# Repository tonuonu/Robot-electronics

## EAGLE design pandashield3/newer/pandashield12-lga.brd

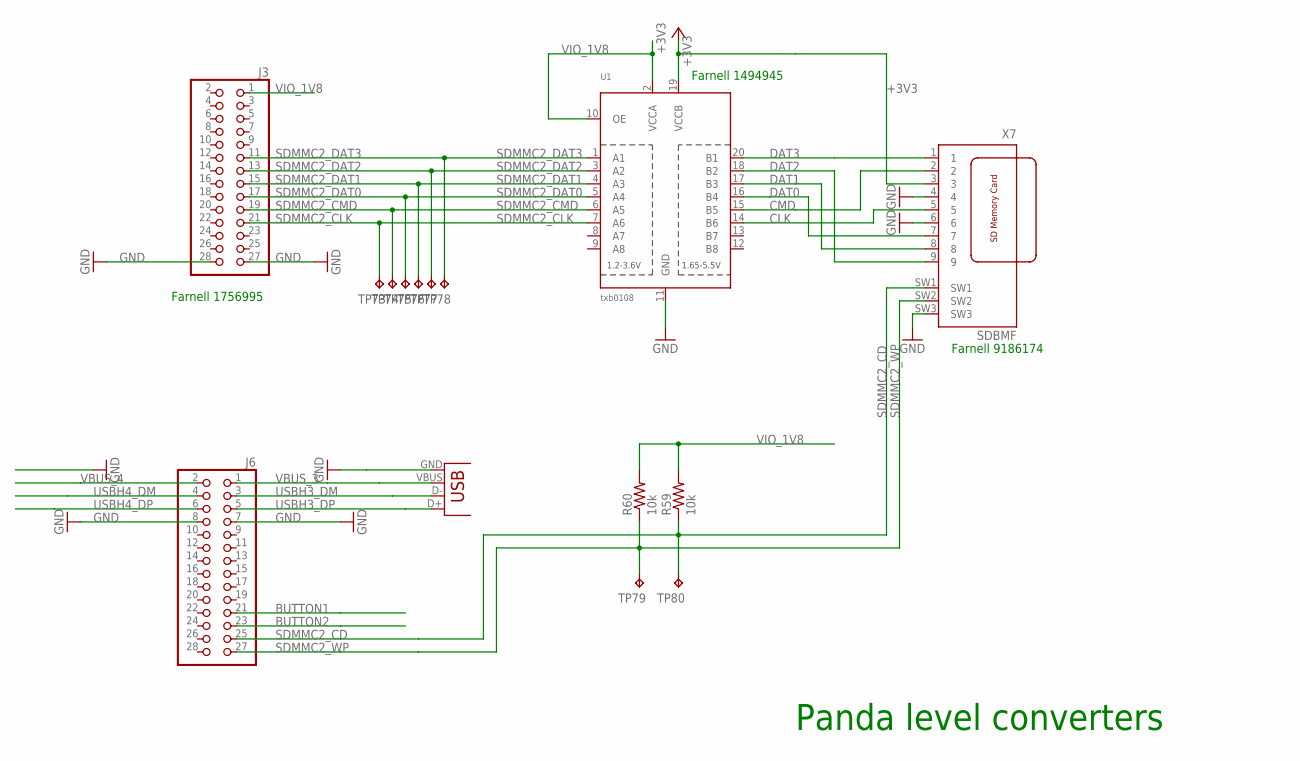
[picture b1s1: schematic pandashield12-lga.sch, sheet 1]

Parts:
J3, J6: PINHD-2X14; 2X14
R59, R60: 10k; R0603
TP73, TP74, TP75, TP76, TP77, TP78, TP79, TP80: TPB1,27; B1,27
U1: txb0108; TSSOP20
X4: USB-A-S
X7: SDBMF; SDBMF-009XXBXX2

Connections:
+3V3: U1.19 (VCCB), X7.3; also elsewhere on the board
BUTTON1: J6.21
BUTTON2: J6.23
CLK: U1.14 (B6), X7.5
CMD: U1.15 (B5), X7.2
DAT0: U1.16 (B4), X7.7
DAT1: U1.17 (B3), X7.8
DAT2: U1.18 (B2), X7.9
DAT3: U1.20 (B1), X7.1
GND: J3.27, J3.28, J6.7, J6.8, U1.11 (GND), X4.GND, X7.4, X7.6, X7.SW3; also elsewhere on the board
SDMMC2_CD: J6.25, R59.1, TP80.TP, X7.SW1
SDMMC2_CLK: J3.21, TP73.TP, U1.7 (A6)
SDMMC2_CMD: J3.19, TP74.TP, U1.6 (A5)
SDMMC2_DAT0: J3.17, TP75.TP, U1.5 (A4)
SDMMC2_DAT1: J3.15, TP76.TP, U1.4 (A3)
SDMMC2_DAT2: J3.13, TP77.TP, U1.3 (A2)
SDMMC2_DAT3: J3.11, TP78.TP, U1.1 (A1)
SDMMC2_WP: J6.27, R60.1, TP79.TP, X7.SW2
USBH3_DM: J6.3, X4.D-
USBH3_DP: J6.5, X4.D+
USBH4_DM: J6.4
USBH4_DP: J6.6
VBUS_3: J6.1, X4.VBUS
VBUS_4: J6.2
VIO_1V8: J3.1, R59.2, R60.2, U1.2 (VCCA), U1.10 (OE)

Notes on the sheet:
Panda level converters
Farnell 1494945
Farnell 9186174
Farnell 1756995

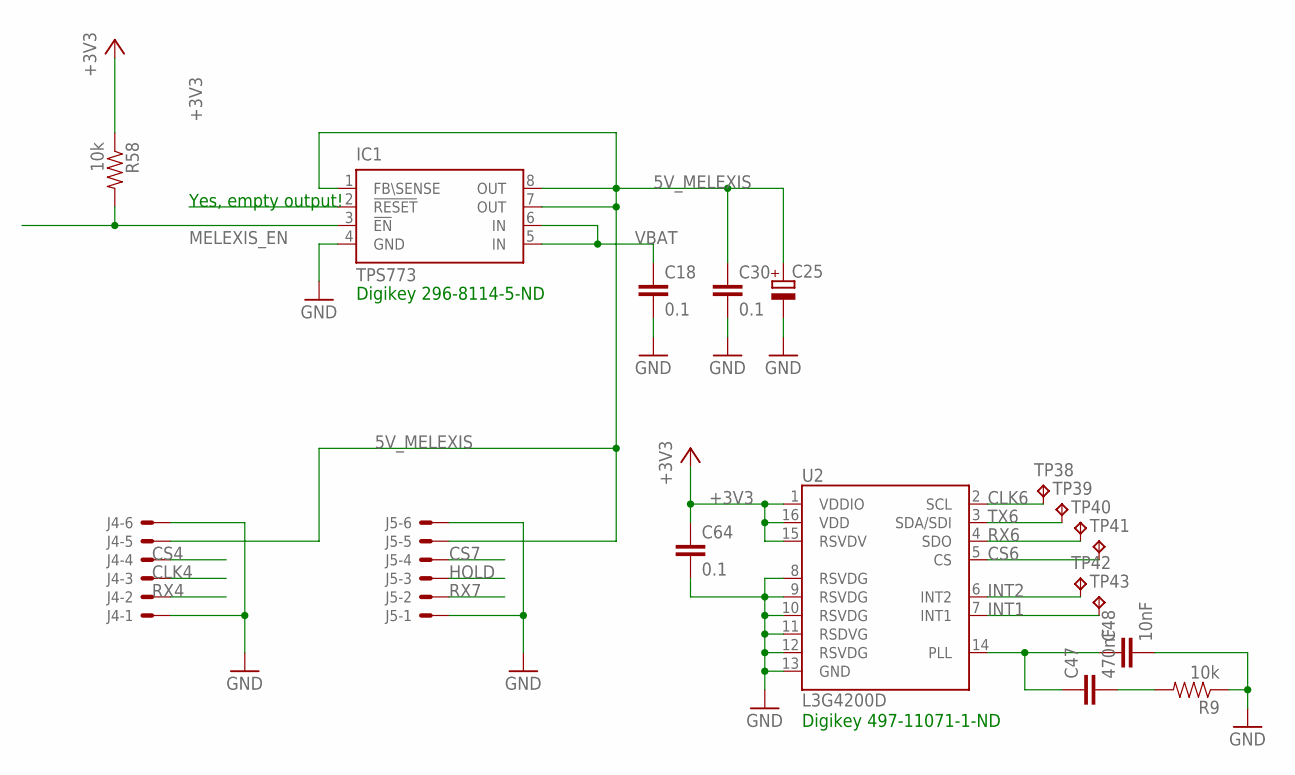
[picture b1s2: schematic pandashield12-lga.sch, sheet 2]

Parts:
C18, C30: 0.1; C0603
C25: CPOL-EUD/7343-31R; D/7343-31R
C47: 470nF; 0603-CAP
C48: 10nF; 0603-CAP
C64: 0.1; 0603-CAP
IC1: TPS773; MSOP8
J4, J5: XF2L-0625-1
R9, R58: 10k; 0603-RES
TP38, TP39, TP40, TP41, TP42, TP43: TPB1,27; B1,27
U2: L3G4200D; LGA16-4X4

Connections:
5V_MELEXIS: C25.+, C30.1, IC1.1 (FB\SENSE), IC1.7 (OUT), IC1.8 (OUT), J4.5, J5.5
+3V3: C64.1, R58.1, U2.1 (VDDIO), U2.15 (RSVDV), U2.16 (VDD); also elsewhere on the board
CLK4: J4.3; also elsewhere on the board
CLK6: TP38.TP, U2.2 (SCL); also elsewhere on the board
CS4: J4.4; also elsewhere on the board
CS6: TP41.TP, U2.5 (CS); also elsewhere on the board
CS7: J5.4; also elsewhere on the board
GND: C18.2, C25.-, C30.2, C48.2, C64.2, IC1.4 (GND), J4.1, J4.6, J5.1, J5.6, R9.1, U2.8 (RSVDG), U2.9 (RSVDG), U2.10 (RSVDG), U2.11 (RSDVG), U2.12 (RSVDG), U2.13 (GND); also elsewhere on the board
HOLD: J5.3; also elsewhere on the board
INT1: TP43.TP, U2.7 (INT1); also elsewhere on the board
INT2: TP42.TP, U2.6 (INT2); also elsewhere on the board
MELEXIS_EN: IC1.3 (!EN), R58.2; also elsewhere on the board
unnamed: C47.1, C48.1, U2.14 (PLL)
unnamed: C47.2, R9.2
RX4: J4.2; also elsewhere on the board
RX6: TP40.TP, U2.4 (SDO); also elsewhere on the board
RX7: J5.2; also elsewhere on the board
TX6: TP39.TP, U2.3 (SDA/SDI); also elsewhere on the board
VBAT: C18.1, IC1.5 (IN), IC1.6 (IN); also elsewhere on the board

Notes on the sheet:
Digikey 296-8114-5-ND
Digikey 497-11071-1-ND
Yes, empty output!

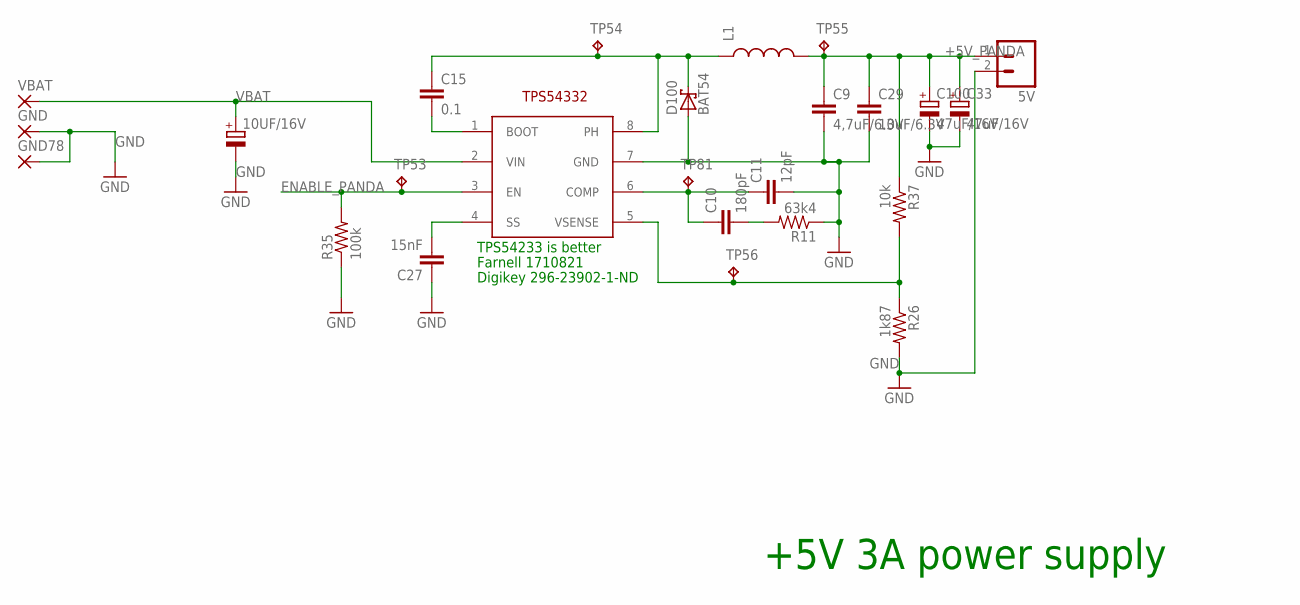
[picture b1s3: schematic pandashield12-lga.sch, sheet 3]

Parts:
5V: M02; 02P
10UF/16V: CPOL-EUC/6032-28R; C/6032-28R
C9: 4,7uF/6.3V; C0805
C10: 180pF; C0603
C11: 12pF; C0603
C15: 0.1; C0603
C27: 15nF; C0603
C29: 10uF/6.3V; 1210
C33, C100: 47uF/16V; C/6032-28R
D100: BAT54; SOT23
GND, GND78: 3,81/1,4
L1: INDUCTORCR75; CR75
R11: 63k4; R0603
R26: 1k87; R0603
R35: 100k; R0603
R37: 10k; R0603
TP53, TP54, TP55, TP56, TP81: TPB1,27; B1,27
U$3: TPS54233; SO8
VBAT: 3,81/1,4

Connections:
+5V_PANDA: 5V.1, C9.1, C29.1, C33.+, C100.+, L1.P$2 (2), R37.1, TP55.TP
ENABLE_PANDA: R35.2, TP53.TP, U$3.3 (EN); also elsewhere on the board
GND: 5V.2, 10UF/16V.-, C9.2, C11.2, C27.1, C29.2, C33.-, C100.-, D100.1 (A), GND.1, GND78.1, R11.1, R26.2, R35.1, U$3.7 (GND); also elsewhere on the board
unnamed: C10.1, C11.1, TP81.TP, U$3.6 (COMP)
unnamed: C10.2, R11.2
unnamed: C27.2, U$3.4 (SS)
unnamed: C15.2, U$3.1 (BOOT)
unnamed: R26.1, R37.2, TP56.TP, U$3.5 (VSENSE)
unnamed: C15.1, D100.3 (C), L1.P$1 (1), TP54.TP, U$3.8 (PH)
VBAT: 10UF/16V.+, U$3.2 (VIN), VBAT.1; also elsewhere on the board

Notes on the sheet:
+5V 3A power supply
TPS54233 is better
Farnell 1710821
Digikey 296-23902-1-ND

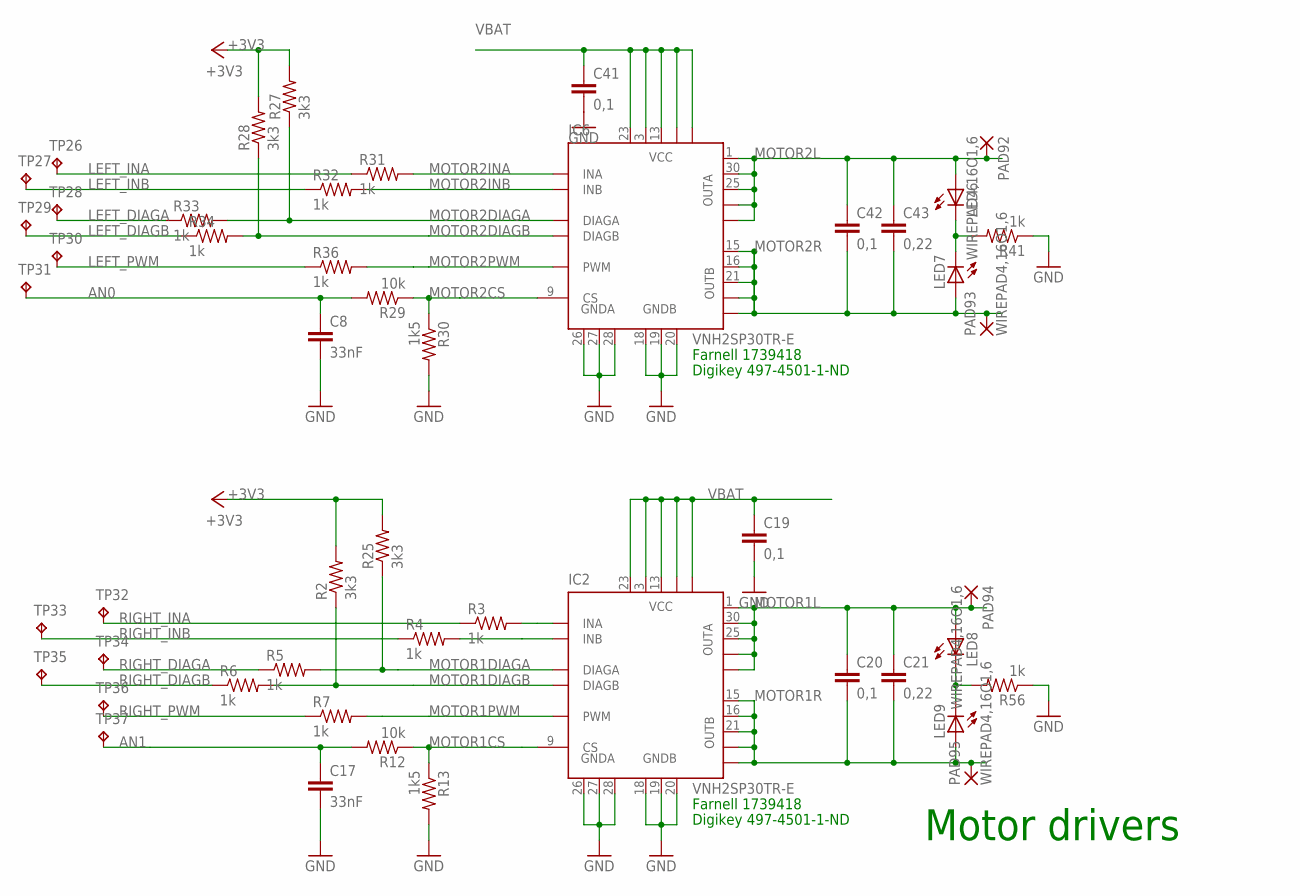
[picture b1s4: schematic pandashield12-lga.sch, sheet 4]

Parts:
C8, C17: 33nF; 0603-CAP
C19, C20, C41, C42: 0,1; 0603-CAP
C21, C43: 0,22; 0603-CAP
IC2, IC6: VNH2SP30TR-E; MULTIPOWERSO-30
LED6, LED7, LED8, LED9: LEDCHIP-LED0603; CHIP-LED0603
PAD92, PAD93, PAD94, PAD95: WIREPAD4,16O1,6; 4,16O1,6
R2, R25, R27, R28: 3k3; 0603-RES
R3, R4, R5, R6, R7, R31, R32, R33, R34, R36, R41, R56: 1k; 0603-RES
R12, R29: 10k; 0603-RES
R13, R30: 1k5; 0603-RES
TP26, TP27, TP28, TP29, TP30, TP31, TP32, TP33, TP34, TP35, TP36, TP37: TPB1,27; B1,27

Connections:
+3V3: R2.2, R25.2, R27.2, R28.2; also elsewhere on the board
AN0: C8.1, R29.2, TP31.TP; also elsewhere on the board
AN1: C17.1, R12.2, TP37.TP; also elsewhere on the board
GND: C8.2, C17.2, C19.2, C41.2, IC2.18 (GNDB), IC2.19 (GNDB), IC2.20 (GNDB), IC2.26 (GNDA), IC2.27 (GNDA), IC2.28 (GNDA), IC6.18 (GNDB), IC6.19 (GNDB), IC6.20 (GNDB), IC6.26 (GNDA), IC6.27 (GNDA), IC6.28 (GNDA), R13.2, R30.2, R41.1, R56.1; also elsewhere on the board
LEFT_DIAGA: R33.1, TP28.TP; also elsewhere on the board
LEFT_DIAGB: R34.1, TP29.TP; also elsewhere on the board
LEFT_INA: R31.1, TP26.TP; also elsewhere on the board
LEFT_INB: R32.1, TP27.TP; also elsewhere on the board
LEFT_PWM: R36.1, TP30.TP; also elsewhere on the board
MOTOR1CS: IC2.9 (CS), R12.1, R13.1
MOTOR1DIAGA: IC2.6 (DIAGA), R5.2, R25.1
MOTOR1DIAGB: IC2.10 (DIAGB), R2.1, R6.2
MOTOR1INA: IC2.5 (INA), R3.2
MOTOR1INB: IC2.11 (INB), R4.2
MOTOR1L: C20.1, C21.1, IC2.1 (OUTA), IC2.25 (OUTA), IC2.30 (OUTA), IC2.OUTA, IC2.OUTA@1 (OUTA), LED8.A, PAD94.1; also elsewhere on the board
MOTOR1PWM: IC2.8 (PWM), R7.2
MOTOR1R: C20.2, C21.2, IC2.15 (OUTB), IC2.16 (OUTB), IC2.21 (OUTB), IC2.OUTB, IC2.OUTB@1 (OUTB), LED9.A, PAD95.1; also elsewhere on the board
MOTOR2CS: IC6.9 (CS), R29.1, R30.1
MOTOR2DIAGA: IC6.6 (DIAGA), R27.1, R33.2
MOTOR2DIAGB: IC6.10 (DIAGB), R28.1, R34.2
MOTOR2INA: IC6.5 (INA), R31.2
MOTOR2INB: IC6.11 (INB), R32.2
MOTOR2L: C42.1, C43.1, IC6.1 (OUTA), IC6.25 (OUTA), IC6.30 (OUTA), IC6.OUTA, IC6.OUTA@1 (OUTA), LED6.A, PAD92.1; also elsewhere on the board
MOTOR2PWM: IC6.8 (PWM), R36.2
MOTOR2R: C42.2, C43.2, IC6.15 (OUTB), IC6.16 (OUTB), IC6.21 (OUTB), IC6.OUTB, IC6.OUTB@1 (OUTB), LED7.A, PAD93.1; also elsewhere on the board
unnamed: LED6.C, LED7.C, R41.2
unnamed: LED8.C, LED9.C, R56.2
RIGHT_DIAGA: R5.1, TP34.TP; also elsewhere on the board
RIGHT_DIAGB: R6.1, TP35.TP; also elsewhere on the board
RIGHT_INA: R3.1, TP32.TP; also elsewhere on the board
RIGHT_INB: R4.1, TP33.TP; also elsewhere on the board
RIGHT_PWM: R7.1, TP36.TP; also elsewhere on the board
VBAT: C19.1, C41.1, IC2.3 (VCC), IC2.13 (VCC), IC2.23 (VCC), IC2.VCC, IC2.VCC@1 (VCC), IC6.3 (VCC), IC6.13 (VCC), IC6.23 (VCC), IC6.VCC, IC6.VCC@1 (VCC); also elsewhere on the board

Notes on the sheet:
Motor drivers
Farnell 1739418
Digikey 497-4501-1-ND

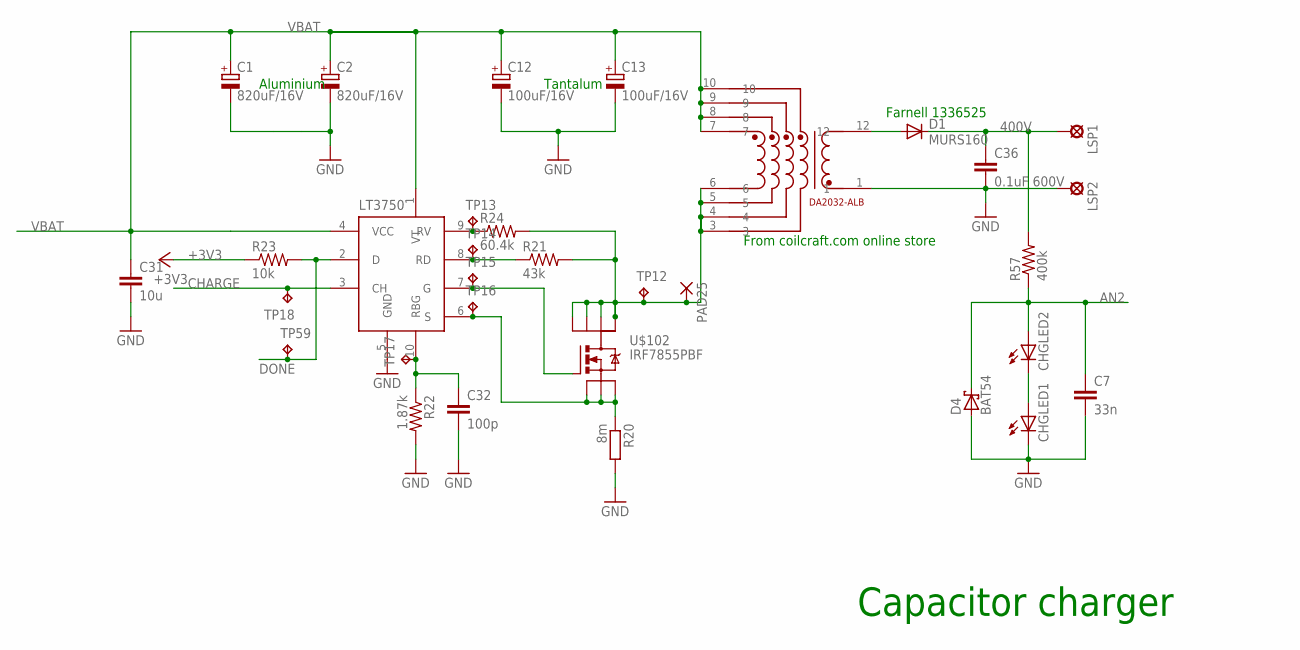
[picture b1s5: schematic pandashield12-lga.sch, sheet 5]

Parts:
C1, C2: 820uF/16V; 153CLV-1014
C7: 33n; 0603-CAP
C12, C13: 100uF/16V; C/6032-28R
C31: 10u; C1210
C32: 100p; 0603-CAP
C36: 0.1uF 600V; C1812
CHGLED1, CHGLED2: LEDCHIPLED_0603; CHIPLED_0603
D1: MURS160; SMB
D4: BAT54; SOT23
LSP1, LSP2: LSP11
LT3750: LT3750; MSOP
PAD25: 1,6/0,9
R20: 8m; R1210
R21: 43k; 0603-RES
R22: 1.87k; 0603-RES
R23: 10k; 0603-RES
R24: 60.4k; 0603-RES
R57: 400k; R1210
TP12, TP13, TP14, TP15, TP16, TP17, TP18, TP59: TPB1,27; B1,27
U$1: DA2032-ALBDA2032-ALB; DA2032-ALB
U$102: IRF7855PBF; SO8

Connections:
400V: C36.1, D1.C, LSP1.MP, R57.2
+3V3: R23.1; also elsewhere on the board
AN2: C7.1, CHGLED2.A, D4.3 (C), R57.1; also elsewhere on the board
CHARGE: LT3750.3 (CH), TP18.TP; also elsewhere on the board
DONE: LT3750.2 (D), R23.2, TP59.TP; also elsewhere on the board
GND: C1.-, C2.-, C7.2, C12.-, C13.-, C31.2, C32.2, C36.2, CHGLED1.C, D4.1 (A), LSP2.MP, LT3750.5 (GND), R20.2, R22.2, U$1.1; also elsewhere on the board
unnamed: CHGLED1.A, CHGLED2.C
unnamed: D1.A, U$1.12
unnamed: LT3750.7 (G), TP15.TP, U$102.4 (G)
unnamed: LT3750.9 (RV), R24.1, TP13.TP
unnamed: LT3750.8 (RD), R21.1, TP14.TP
unnamed: PAD25.1, R21.2, R24.2, TP12.TP, U$1.3, U$1.4, U$1.5, U$1.6, U$102.5 (D), U$102.6 (D), U$102.7 (D), U$102.8 (D)
unnamed: LT3750.6 (S), R20.1, TP16.TP, U$102.1 (S), U$102.2 (S), U$102.3 (S)
unnamed: C32.1, LT3750.10 (RBG), R22.1, TP17.TP
VBAT: C1.+, C2.+, C12.+, C13.+, C31.1, LT3750.1 (VT), LT3750.4 (VCC), U$1.7, U$1.8, U$1.9, U$1.10; also elsewhere on the board

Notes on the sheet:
Capacitor charger
Farnell 1336525
From coilcraft.com online store
Aluminium
Tantalum

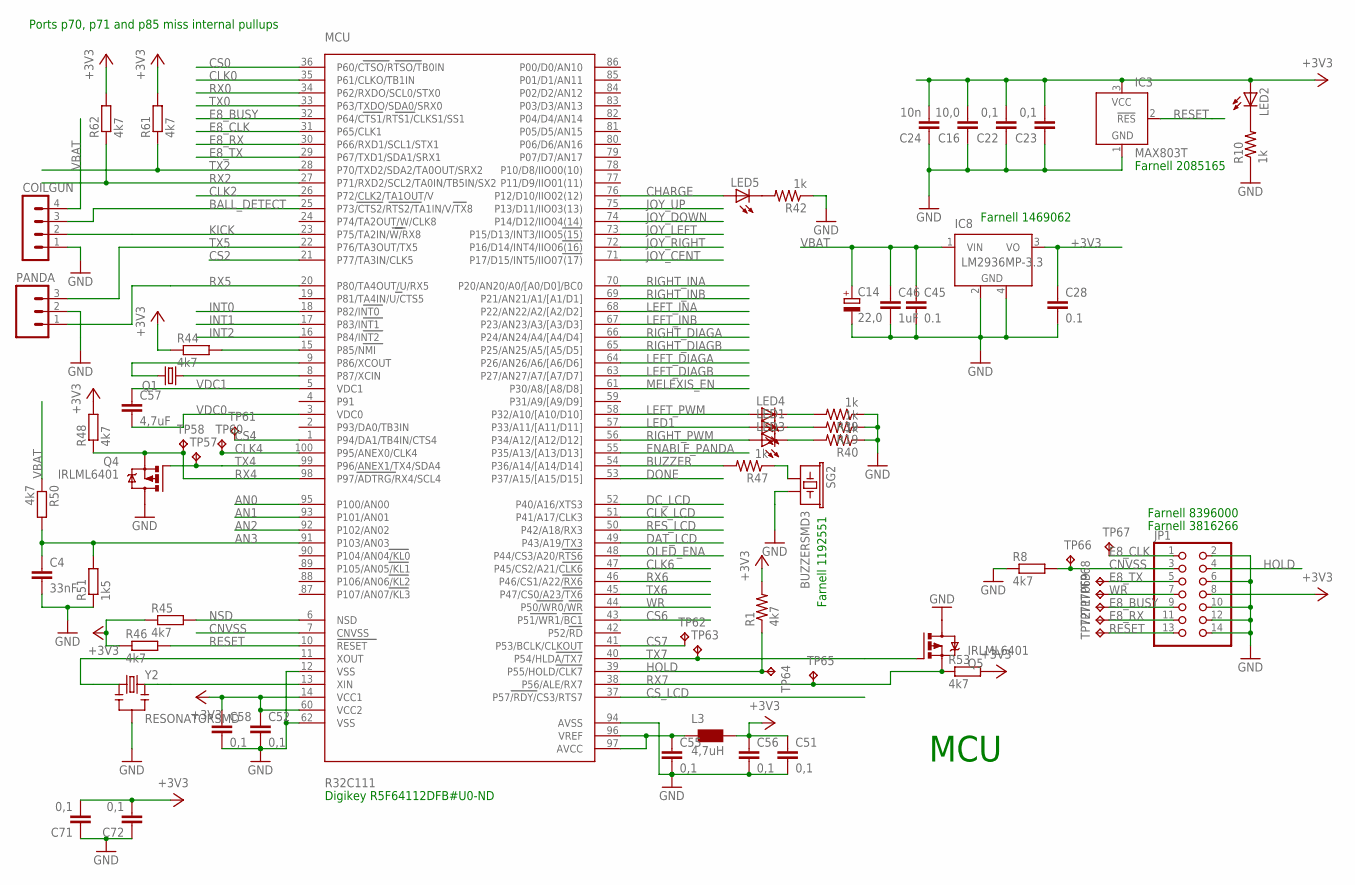
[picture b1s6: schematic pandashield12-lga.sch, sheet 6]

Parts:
C4: 33nF; C0603
C14: 22,0; CT3528
C16: 10,0; C1210
C22, C23, C51, C52, C55, C56, C58, C71, C72: 0,1; C0603
C24: 10n; C0603
C28, C45: 0.1; 0603-CAP
C46: 1uF; 0603-CAP
C57: 4,7uF; C0805K
COILGUN: MA04-1
IC3: MAX803T; SOT23B-3
IC8: LM2936MP-3.3; SOT223
JP1: PINHD-2X7; 2X07
L3: 4,7uH; WE-KI_0805_B
LED1, LED2, LED3, LED4, LED5: LEDCHIP-LED0603; CHIP-LED0603
MCU: R32C111; 100P6Q-A
PANDA: MA03; 03P
Q1: CRYSTALMM20SS; MM20SS
Q4, Q5: IRLML6401; MICRO3
R1: 4k7; 0603-RES
R8, R44, R45, R46, R48, R50, R53, R61, R62: 4k7; R0603
R10, R19, R39, R40, R42, R47: 1k; 0603-RES
R51: 1k5; R0603
SG2: BUZZERSMD3; BUZZER-CMT1102
TP57, TP58, TP60, TP61, TP62, TP63, TP64, TP65, TP66, TP67, TP68, TP69, TP70, TP71, TP72: TPB1,27; B1,27
Y2: RESONATORSMD; RESONATOR-SMD

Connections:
+3V3: C16.2, C22.2, C23.2, C24.2, C28.1, C51.1, C52.1, C56.1, C58.1, C71.2, C72.2, IC3.3 (VCC), IC8.3 (VO), JP1.8, L3.1 (2), LED2.A, MCU.14 (VCC1), MCU.60 (VCC2), R1.2, R44.1, R45.1, R46.1, R48.2, R53.2, R61.2, R62.2; also elsewhere on the board
AN0: MCU.95 (P100/AN00); also elsewhere on the board
AN1: MCU.93 (P101/AN01); also elsewhere on the board
AN2: MCU.92 (P102/AN02); also elsewhere on the board
AN3: C4.1, MCU.91 (P103/AN03), R50.2, R51.2
BALL_DETECT: COILGUN.3, MCU.25 (P73/CTS2/RTS2/TA1IN/V/TX8)
BUZZER: MCU.54 (P36/A14/[A14/D14]), R47.2
CHARGE: LED5.A, MCU.76 (P12/D10/IIO02(12)); also elsewhere on the board
CLK0: MCU.35 (P61/CLKO/TB1IN); also elsewhere on the board
CLK2: MCU.26 (P72/CLK2/TA1OUT/V); also elsewhere on the board
CLK4: MCU.100 (P95/ANEX0/CLK4), TP60.TP; also elsewhere on the board
CLK6: MCU.47 (P45/CS2/A21/CLK6); also elsewhere on the board
CLK_LCD: MCU.51 (P41/A17/CLK3); also elsewhere on the board
CNVSS: JP1.3, MCU.7 (CNVSS), R8.2, TP66.TP
CS0: MCU.36 (P60/CTSO/RTSO/TB0IN); also elsewhere on the board
CS2: MCU.21 (P77/TA3IN/CLK5); also elsewhere on the board
CS4: MCU.1 (P94/DA1/TB4IN/CTS4), TP61.TP; also elsewhere on the board
CS6: MCU.43 (P51/WR1/BC1); also elsewhere on the board
CS7: MCU.41 (P53/BCLK/CLKOUT), TP62.TP; also elsewhere on the board
CS_LCD: MCU.37 (P57/RDY/CS3/RTS7); also elsewhere on the board
DAT_LCD: MCU.49 (P43/A19/TX3); also elsewhere on the board
DC_LCD: MCU.52 (P40/A16/XTS3); also elsewhere on the board
DONE: MCU.53 (P37/A15/[A15/D15]); also elsewhere on the board
E8_BUSY: JP1.9, MCU.32 (P64/CTS1/RTS1/CLKS1/SS1), TP70.TP
E8_CLK: JP1.1, MCU.31 (P65/CLK1), TP67.TP
E8_RX: JP1.11, MCU.30 (P66/RXD1/SCL1/STX1), TP71.TP
E8_TX: JP1.5, MCU.29 (P67/TXD1/SDA1/SRX1), TP68.TP
ENABLE_PANDA: MCU.55 (P35/A13/[A13/D13]); also elsewhere on the board
GND: C4.2, C14.-, C16.1, C22.1, C23.1, C24.1, C28.2, C45.2, C46.2, C51.2, C52.2, C55.2, C56.2, C58.2, C71.1, C72.1, COILGUN.1, IC3.1 (GND), IC8.2 (GND), IC8.4 (GND), JP1.2, JP1.6, JP1.10, JP1.12, JP1.14, MCU.12 (VSS), MCU.62 (VSS), MCU.94 (AVSS), PANDA.2, Q4.3 (D), Q5.3 (D), R8.1, R10.1, R19.1, R39.1, R40.1, R42.1, R51.1, SG2.2, Y2.2; also elsewhere on the board
HOLD: JP1.4, MCU.39 (P55/HOLD/CLK7), R1.1, TP64.TP; also elsewhere on the board
INT0: MCU.18 (P82/INT0); also elsewhere on the board
INT1: MCU.17 (P83/INT1); also elsewhere on the board
INT2: MCU.16 (P84/INT2); also elsewhere on the board
JOY_CENT: MCU.71 (P17/D15/INT5/IIO07(17)); also elsewhere on the board
JOY_DOWN: MCU.74 (P14/D12/IIO04(14)); also elsewhere on the board
JOY_LEFT: MCU.73 (P15/D13/INT3/IIO05(15)); also elsewhere on the board
JOY_RIGHT: MCU.72 (P16/D14/INT4/IIO06(16)); also elsewhere on the board
JOY_UP: MCU.75 (P13/D11/IIO03(13)); also elsewhere on the board
KICK: COILGUN.2, MCU.23 (P75/TA2IN/W/RX8)
LED1: LED1.A, MCU.57 (P33/A11/[A11/D11])
LEFT_DIAGA: MCU.64 (P26/AN26/A6/[A6/D6]); also elsewhere on the board
LEFT_DIAGB: MCU.63 (P27/AN27/A7/[A7/D7]); also elsewhere on the board
LEFT_INA: MCU.68 (P22/AN22/A2/[A2/D2]); also elsewhere on the board
LEFT_INB: MCU.67 (P23/AN23/A3/[A3/D3]); also elsewhere on the board
LEFT_PWM: LED4.A, MCU.58 (P32/A10/[A10/D10]); also elsewhere on the board
MELEXIS_EN: MCU.61 (P30/A8/[A8/D8]); also elsewhere on the board
unnamed: LED3.C, R40.2
unnamed: LED1.C, R19.2
unnamed: LED4.C, R39.2
unnamed: LED5.C, R42.2
unnamed: R47.1, SG2.1
unnamed: MCU.15 (P85/NMI), R44.2
unnamed: MCU.8 (P87/XCIN), Q1.1
unnamed: LED2.C, R10.2
NSD: MCU.6 (NSD), R45.2
OLED_ENA: MCU.48 (P44/CS3/A20/RTS6); also elsewhere on the board
RESET: IC3.2 (!RES), JP1.13, MCU.10 (RESET), R46.2, TP72.TP
RES_LCD: MCU.50 (P42/A18/RX3); also elsewhere on the board
RIGHT_DIAGA: MCU.66 (P24/AN24/A4/[A4/D4]); also elsewhere on the board
RIGHT_DIAGB: MCU.65 (P25/AN25/A5/[A5/D5]); also elsewhere on the board
RIGHT_INA: MCU.70 (P20/AN20/A0/[A0/D0]/BC0); also elsewhere on the board
RIGHT_INB: MCU.69 (P21/AN21/A1/[A1/D1]); also elsewhere on the board
RIGHT_PWM: LED3.A, MCU.56 (P34/A12/[A12/D12]); also elsewhere on the board
RX0: MCU.34 (P62/RXDO/SCL0/STX0); also elsewhere on the board
RX2: MCU.27 (P71/RXD2/SCL2/TA0IN/TB5IN/SX2), R62.1; also elsewhere on the board
RX4: MCU.98 (P97/ADTRG/RX4/SCL4), Q4.2 (S), R48.1, TP58.TP; also elsewhere on the board
RX5: MCU.20 (P80/TA4OUT/U/RX5), PANDA.1
RX6: MCU.46 (P46/CS1/A22/RX6); also elsewhere on the board
RX7: MCU.38 (P56/ALE/RX7), Q5.2 (S), R53.1, TP65.TP; also elsewhere on the board
TX0: MCU.33 (P63/TXDO/SDA0/SRX0); also elsewhere on the board
TX2: MCU.28 (P70/TXD2/SDA2/TA0OUT/SRX2), R61.1; also elsewhere on the board
TX4: MCU.99 (P96/ANEX1/TX4/SDA4), Q4.1 (G), TP57.TP
TX5: MCU.22 (P76/TA3OUT/TX5), PANDA.3
TX6: MCU.45 (P47/CS0/A23/TX6); also elsewhere on the board
TX7: MCU.40 (P54/HLDA/TX7), Q5.1 (G), TP63.TP
UCREF: C55.1, L3.2 (1), MCU.96 (VREF), MCU.97 (AVCC)
VBAT: C14.+, C45.1, C46.1, COILGUN.4, IC8.1 (VIN), R50.1; also elsewhere on the board
VDC0: C57.2, MCU.3 (VDC0)
VDC1: C57.1, MCU.5 (VDC1)
WR: JP1.7, MCU.44 (P50/WR0/WR), TP69.TP
XCOUT: MCU.9 (P86/XCOUT), Q1.4 (2)
XIN: MCU.13 (XIN), Y2.3
XOUT: MCU.11 (XOUT), Y2.1

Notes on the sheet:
MCU
Farnell 1469062
Farnell 1192551
Farnell 8396000
Farnell 3816266
Farnell 2085165
Digikey R5F64112DFB#U0-ND
Ports p70, p71 and p85 miss internal pullups

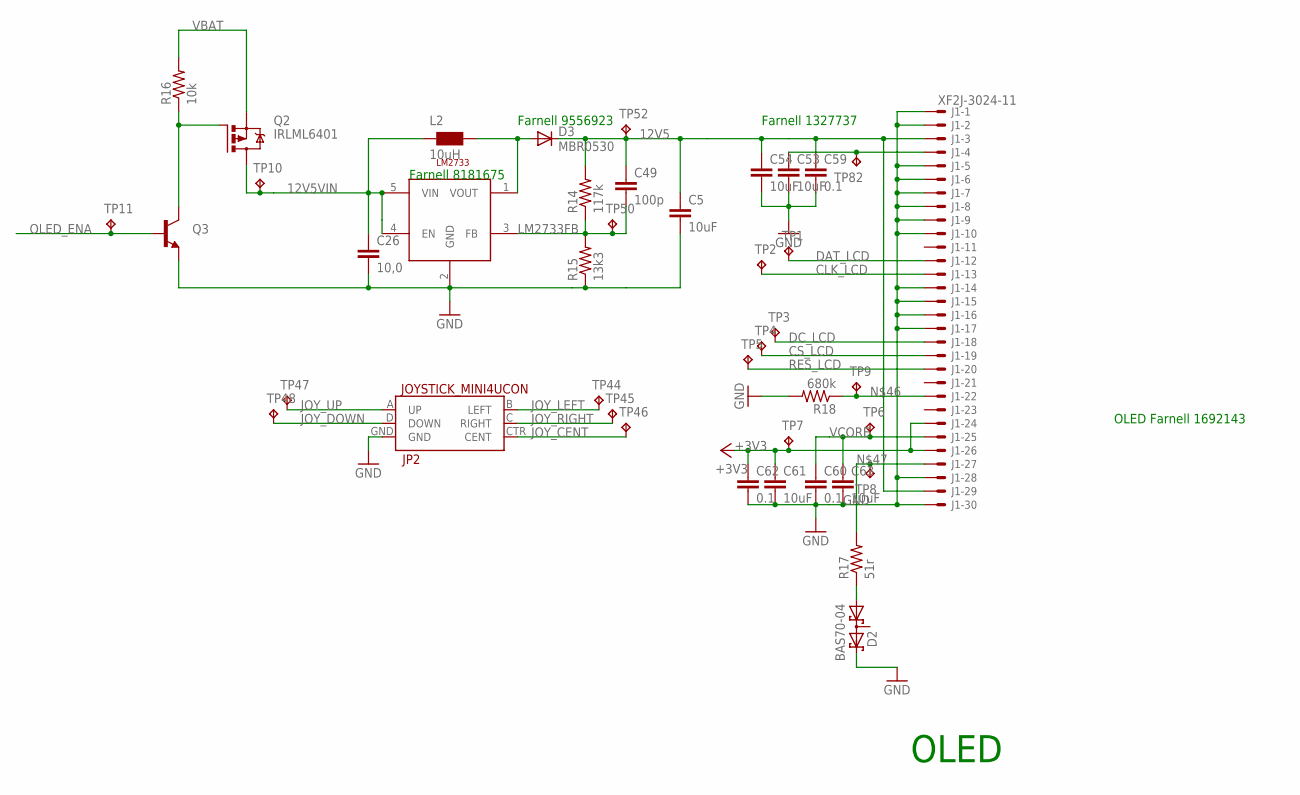
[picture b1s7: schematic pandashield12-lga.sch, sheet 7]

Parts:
C5, C53, C54, C61, C63: 10uF; 1210
C26: 10,0; 1210
C49: 100p; 0603-CAP
C59, C60, C62: 0.1; 0603-CAP
D2: BAS70-04; SOT23
D3: MBR0530; SOD123
J1: XF2J-3024-11
JP2: JOYSTICK_MINI4UCON; JOYSTICK_MINI
L2: 10uH; WE-KI_0805_B
Q2: IRLML6401; MICRO3
Q3: TRANSISTOR_NPNSOT23-3; SOT23-3
R14: 117k; 0603-RES
R15: 13k3; 0603-RES
R16: 10k; 0603-RES
R17: 51r; 0603-RES
R18: 680k; 0603-RES
TP1, TP2, TP3, TP4, TP5, TP6, TP7, TP8, TP9, TP10, TP11, TP44, TP45, TP46, TP47, TP48, TP50, TP52, TP82: TPB1,27; B1,27
U$2: LM2733; SOT23-DBV

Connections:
12V5: C5.1, C49.1, C54.1, C59.1, D3.C, J1.3 (MS), J1.29 (MS), R14.2, TP52.TP
12V5VIN: C26.1, L2.2 (1), Q2.3 (D), TP10.TP, U$2.4 (EN), U$2.5 (VIN)
+3V3: C61.1, C62.1, J1.24 (MS), J1.26 (MS), TP7.TP; also elsewhere on the board
CLK_LCD: J1.13 (MS), TP2.TP; also elsewhere on the board
CS_LCD: J1.19 (MS), TP4.TP; also elsewhere on the board
DAT_LCD: J1.12 (MS), TP1.TP; also elsewhere on the board
DC_LCD: J1.18 (MS), TP3.TP; also elsewhere on the board
GND: C5.2, C26.2, C53.2, C54.2, C59.2, C60.2, C61.2, C62.2, C63.2, D2.2 (C2), J1.1 (MSV), J1.2 (MS), J1.5 (MS), J1.6 (MS), J1.7 (MS), J1.8 (MS), J1.9 (MS), J1.10 (MS), J1.14 (MS), J1.15 (MS), J1.16 (MS), J1.17 (MS), J1.28 (MS), J1.30 (MS), JP2.GND, Q3.2 (E), R15.1, R18.2, U$2.2 (GND); also elsewhere on the board
JOY_CENT: JP2.CTR (CENT), TP46.TP; also elsewhere on the board
JOY_DOWN: JP2.D (DOWN), TP48.TP; also elsewhere on the board
JOY_LEFT: JP2.B (LEFT), TP44.TP; also elsewhere on the board
JOY_RIGHT: JP2.C (RIGHT), TP45.TP; also elsewhere on the board
JOY_UP: JP2.A (UP), TP47.TP; also elsewhere on the board
LM2733FB: C49.2, R14.1, R15.2, TP50.TP, U$2.3 (FB)
unnamed: D2.1 (A1), R17.1
unnamed: C53.1, J1.4 (MS), TP82.TP
unnamed: Q2.1 (G), Q3.3 (C), R16.1
unnamed: J1.22 (MS), R18.1, TP9.TP
unnamed: J1.27 (MS), R17.2, TP8.TP
unnamed: D3.A, L2.1 (2), U$2.1 (VOUT)
OLED_ENA: Q3.1 (B), TP11.TP; also elsewhere on the board
RES_LCD: J1.20 (MS), TP5.TP; also elsewhere on the board
VBAT: Q2.2 (S), R16.2; also elsewhere on the board
VCORE: C60.1, C63.1, J1.25 (MS), TP6.TP

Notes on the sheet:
OLED
Farnell 8181675
Farnell 9556923
Farnell 1327737
OLED Farnell 1692143

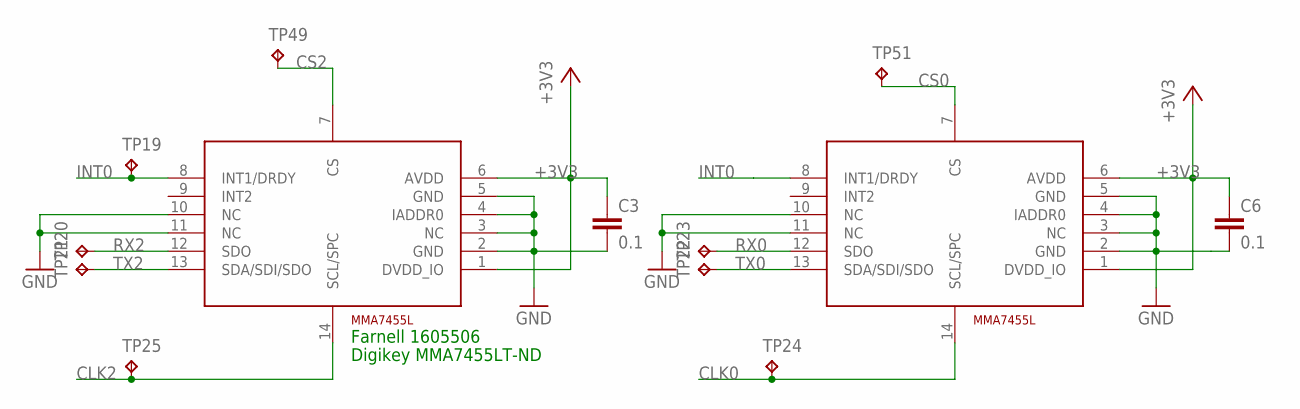
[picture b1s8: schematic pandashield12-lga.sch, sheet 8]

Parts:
C3, C6: 0.1; 0603-CAP
TP19, TP20, TP21, TP22, TP23, TP24, TP25, TP49, TP51: TPB1,27; B1,27
U$5, U$6: MMA7455L; LGA14

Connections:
+3V3: C3.1, C6.1, U$5.1 (DVDD_IO), U$5.6 (AVDD), U$6.1 (DVDD_IO), U$6.6 (AVDD); also elsewhere on the board
CLK0: TP24.TP, U$6.14 (SCL/SPC); also elsewhere on the board
CLK2: TP25.TP, U$5.14 (SCL/SPC); also elsewhere on the board
CS0: TP51.TP, U$6.7 (CS); also elsewhere on the board
CS2: TP49.TP, U$5.7 (CS); also elsewhere on the board
GND: C3.2, C6.2, U$5.2 (GND), U$5.3 (NC), U$5.4 (IADDR0), U$5.5 (GND), U$5.10 (NC), U$5.11 (NC), U$6.2 (GND), U$6.3 (NC), U$6.4 (IADDR0), U$6.5 (GND), U$6.10 (NC), U$6.11 (NC); also elsewhere on the board
INT0: TP19.TP, U$5.8 (INT1/DRDY), U$6.8 (INT1/DRDY); also elsewhere on the board
RX0: TP23.TP, U$6.12 (SDO); also elsewhere on the board
RX2: TP20.TP, U$5.12 (SDO); also elsewhere on the board
TX0: TP22.TP, U$6.13 (SDA/SDI/SDO); also elsewhere on the board
TX2: TP21.TP, U$5.13 (SDA/SDI/SDO); also elsewhere on the board

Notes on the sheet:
Farnell 1605506
Digikey MMA7455LT-ND

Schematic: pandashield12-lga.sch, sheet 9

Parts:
PAD3, PAD4, PAD7, PAD8, PAD9, PAD10, PAD11, PAD12, PAD13, PAD14, PAD15, PAD16, PAD17, PAD18, PAD19, PAD20, PAD21, PAD22, PAD23, PAD24: 1,6/0,9
PAD26, PAD27, PAD28, PAD29, PAD30, PAD31, PAD32, PAD33, PAD34, PAD35, PAD36, PAD37, PAD38, PAD39, PAD40, PAD41, PAD42, PAD43, PAD44, PAD45, PAD46, PAD47, PAD48, PAD49, PAD50, PAD51, PAD52, PAD53, PAD54, PAD55, PAD56, PAD57, PAD58, PAD59, PAD60, PAD61, PAD62, PAD63, PAD64, PAD65, PAD66, PAD67, PAD68, PAD69, PAD70, PAD71, PAD72, PAD73, PAD74, PAD75, PAD76, PAD77, PAD78, PAD79, PAD80, PAD81, PAD82, PAD83, PAD84, PAD85, PAD86, PAD87, PAD88, PAD89, PAD90, PAD91: WIREPAD1,6/0,8; 1,6/0,8

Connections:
GND: PAD3.1, PAD4.1, PAD7.1, PAD8.1, PAD9.1, PAD10.1, PAD11.1, PAD12.1, PAD13.1, PAD14.1, PAD15.1, PAD16.1, PAD17.1, PAD18.1, PAD19.1, PAD20.1, PAD21.1, PAD22.1, PAD23.1, PAD24.1; also elsewhere on the board
MOTOR1L: PAD56.1, PAD57.1, PAD58.1, PAD59.1, PAD60.1, PAD61.1, PAD62.1, PAD63.1, PAD64.1; also elsewhere on the board
MOTOR1R: PAD65.1, PAD66.1, PAD67.1, PAD68.1, PAD69.1, PAD70.1, PAD71.1, PAD72.1, PAD73.1; also elsewhere on the board
MOTOR2L: PAD74.1, PAD75.1, PAD76.1, PAD77.1, PAD78.1, PAD79.1, PAD80.1, PAD81.1, PAD82.1; also elsewhere on the board
MOTOR2R: PAD83.1, PAD84.1, PAD85.1, PAD86.1, PAD87.1, PAD88.1, PAD89.1, PAD90.1, PAD91.1; also elsewhere on the board
VBAT: PAD26.1, PAD27.1, PAD28.1, PAD29.1, PAD30.1, PAD31.1, PAD32.1, PAD33.1, PAD34.1, PAD35.1, PAD36.1, PAD37.1, PAD38.1, PAD39.1, PAD40.1, PAD41.1, PAD42.1, PAD43.1, PAD44.1, PAD45.1, PAD46.1, PAD47.1, PAD48.1, PAD49.1, PAD50.1, PAD51.1, PAD52.1, PAD53.1, PAD54.1, PAD55.1; also elsewhere on the board
